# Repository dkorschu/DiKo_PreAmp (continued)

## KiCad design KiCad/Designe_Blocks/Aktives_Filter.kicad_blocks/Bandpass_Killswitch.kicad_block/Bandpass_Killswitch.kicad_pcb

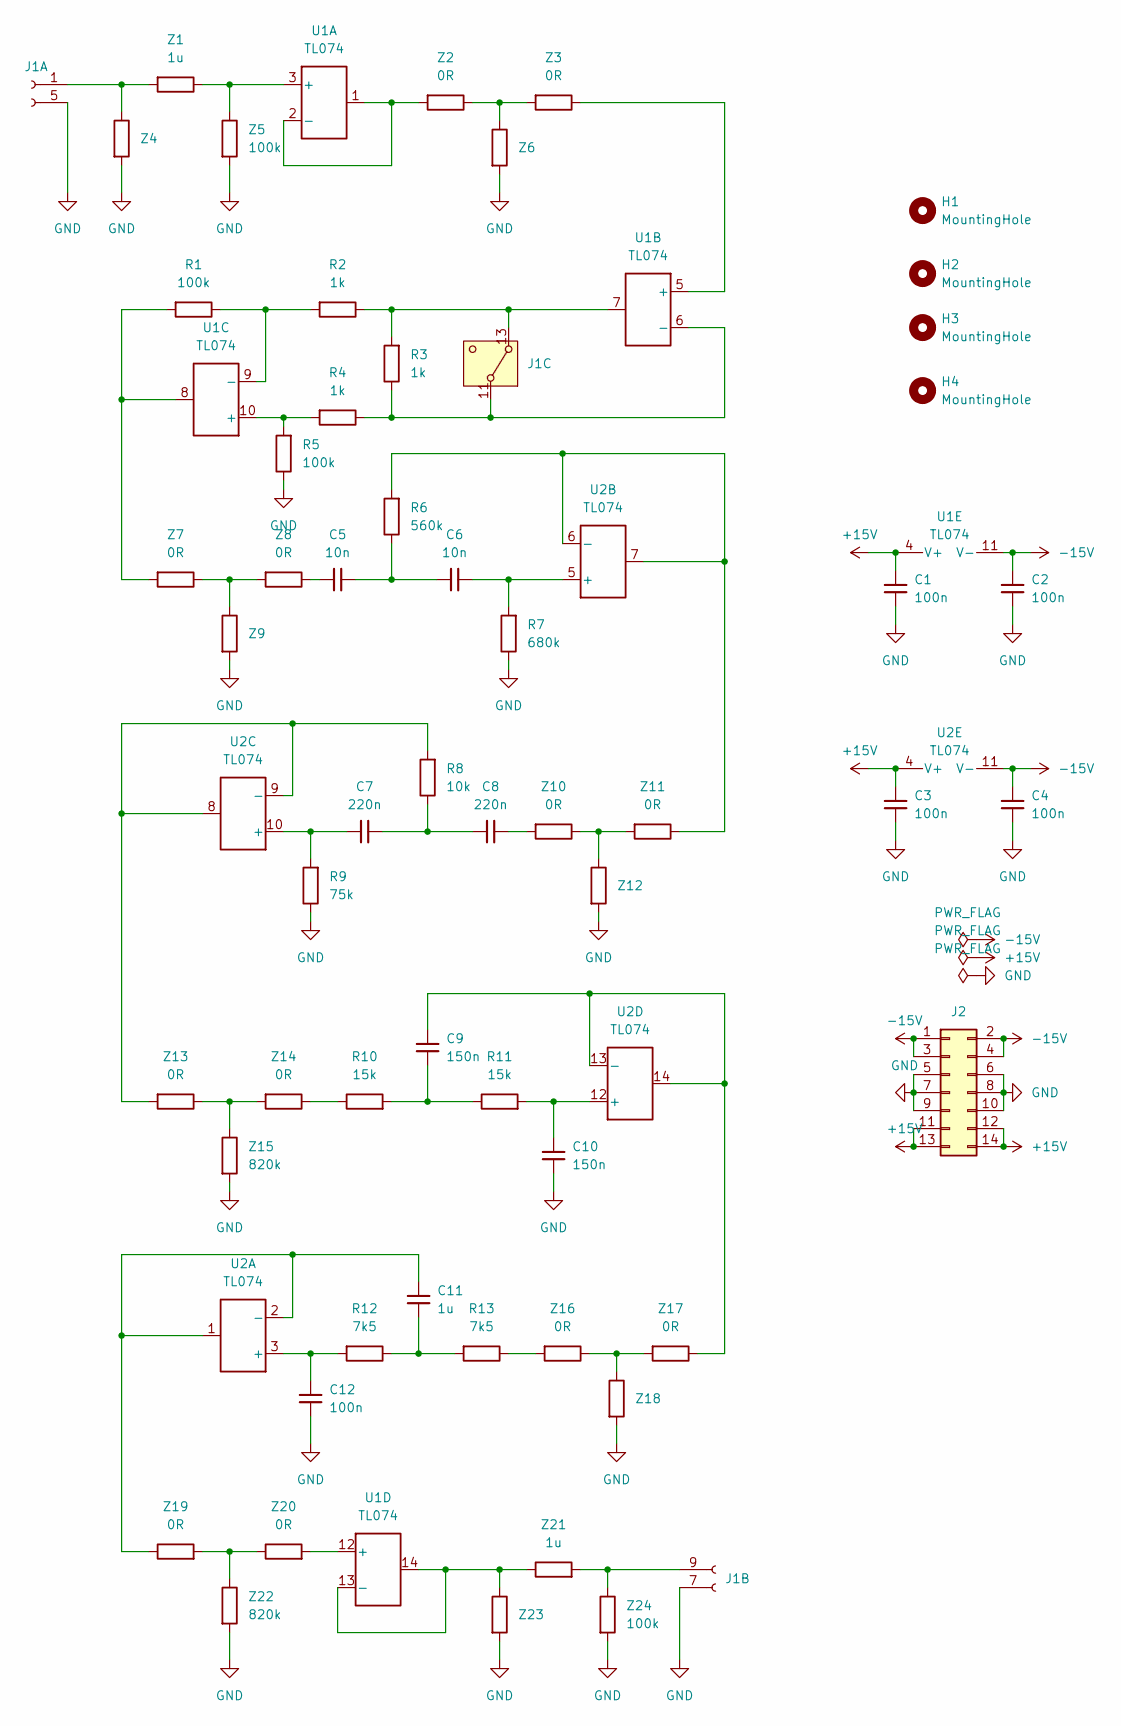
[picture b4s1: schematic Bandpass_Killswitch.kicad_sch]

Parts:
C1, C2, C3, C4, C12: 100n
C5, C6: 10n
C7, C8: 220n
C9, C10: 150n
C11: 1u
H1, H2, H3, H4: MountingHole
J1: Stecker_In_Out_Switch
J2: Conn_02x07_Odd_Even
R1, R5: 100k
R2, R3, R4: 1k
R6: 560k
R7: 680k
R8: 10k
R9: 75k
R10, R11: 15k
R12, R13: 7k5
U1, U2: TL074
Z1, Z21: 1u
Z2, Z3, Z7, Z8, Z10, Z11, Z13, Z14, Z16, Z17, Z19, Z20: 0R
Z4, Z6, Z9, Z12, Z18, Z23: (no value)
Z5, Z24: 100k
Z15, Z22: 820k

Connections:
+15V: C1.2, C3.2, J2.11, J2.12, J2.13, J2.14, U1.4 (V+), U2.4 (V+)
-15V: C2.2, C4.2, J2.1, J2.2, J2.3, J2.4, U1.11 (V-), U2.11 (V-)
unnamed: C5.1, Z8.1
unnamed: C5.2, C6.1, R6.1
unnamed: C7.1, C8.2, R8.1
unnamed: C8.1, Z10.2
unnamed: C9.1, R10.2, R11.1
unnamed: C11.1, R12.1, R13.2
unnamed: J1.9, J1.10, Z21.2, Z24.1
unnamed: J1.11 (SW_In), J1.12, R3.1, R4.1, U1.6 (-)
unnamed: J1.13 (SW_Out), J1.14, R2.1, R3.2, U1.7
unnamed: R1.2, U1.8, Z7.2
unnamed: R10.1, Z14.1
unnamed: R13.1, Z16.2
unnamed: U1.3 (+), Z1.1, Z5.1
unnamed: U1.1, U1.2 (-), Z2.2
unnamed: U1.5 (+), Z3.1
unnamed: R4.2, R5.2, U1.10 (+)
unnamed: R1.1, R2.2, U1.9 (-)
unnamed: U1.12 (+), Z20.2
unnamed: U1.13 (-), U1.14, Z21.1, Z23.1
unnamed: C12.2, R12.2, U2.3 (+)
unnamed: C11.2, U2.1, U2.2 (-), Z19.1
unnamed: C6.2, R7.2, U2.5 (+)
unnamed: R6.2, U2.6 (-), U2.7, Z11.1
unnamed: C7.2, R9.2, U2.10 (+)
unnamed: R8.2, U2.8, U2.9 (-), Z13.2
unnamed: C10.2, R11.2, U2.12 (+)
unnamed: C9.2, U2.13 (-), U2.14, Z17.1
unnamed: Z2.1, Z3.2, Z6.1
unnamed: Z7.1, Z8.2, Z9.1
unnamed: Z10.1, Z11.2, Z12.1
unnamed: Z13.1, Z14.2, Z15.1
unnamed: Z16.1, Z17.2, Z18.1
unnamed: Z19.2, Z20.1, Z22.1

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
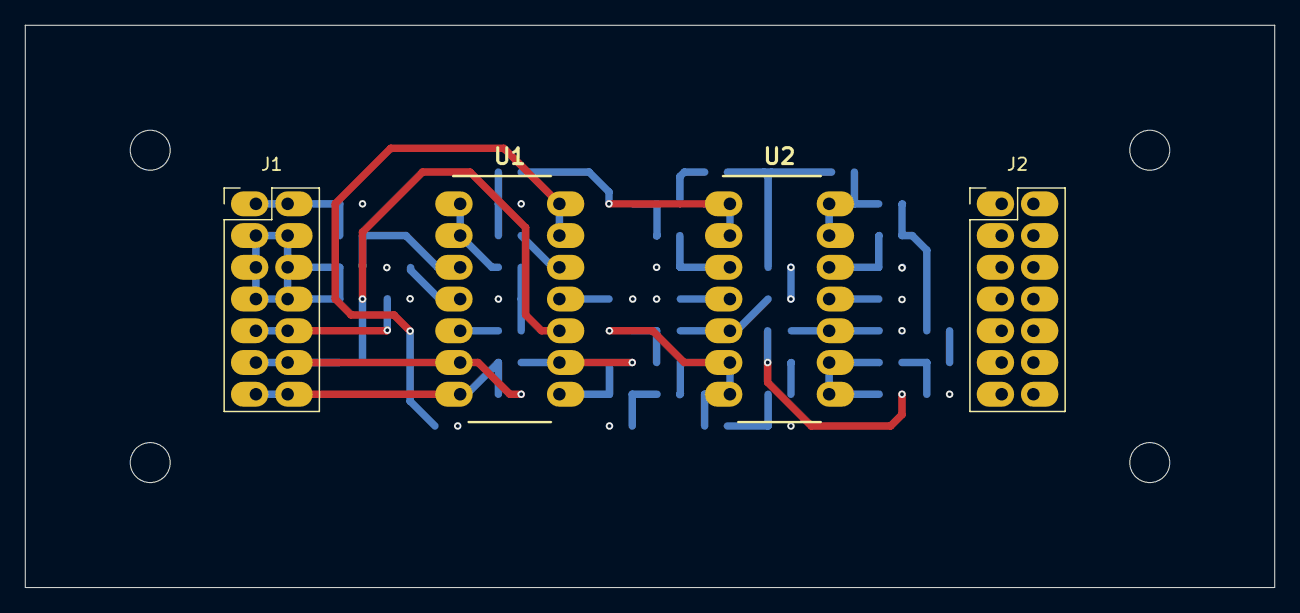
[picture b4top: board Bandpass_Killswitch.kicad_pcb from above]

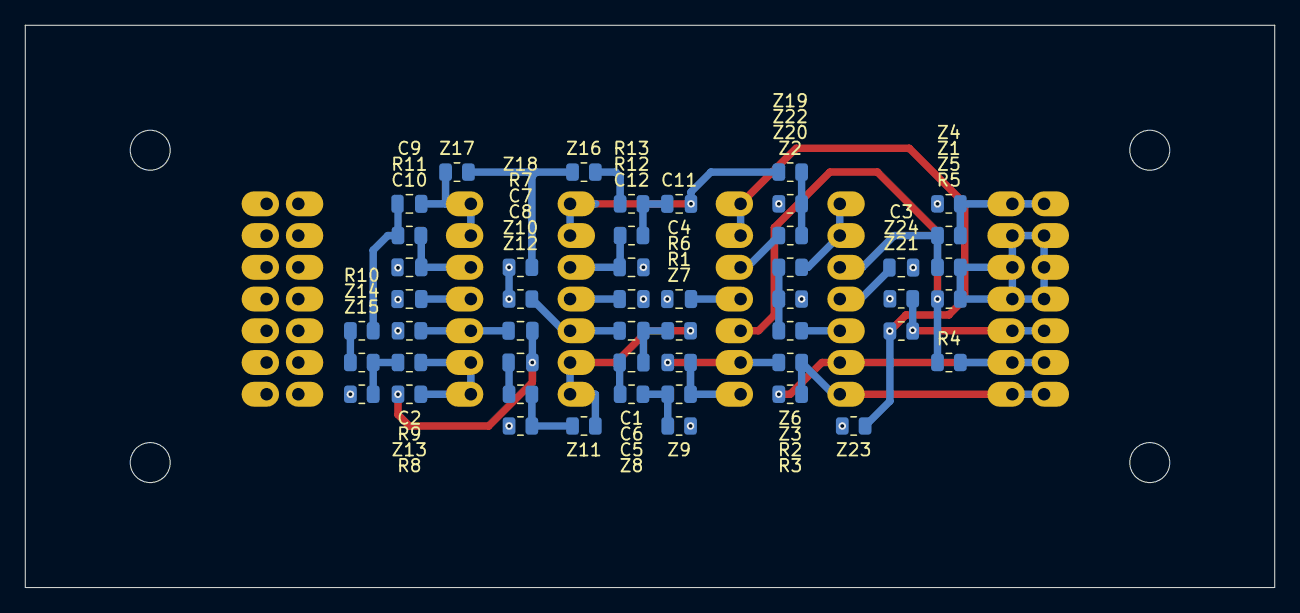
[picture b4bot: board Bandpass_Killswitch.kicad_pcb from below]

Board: 4 copper layers, 100.0 x 45.0 mm, 57 parts (49 on the bottom side), 37 nets.

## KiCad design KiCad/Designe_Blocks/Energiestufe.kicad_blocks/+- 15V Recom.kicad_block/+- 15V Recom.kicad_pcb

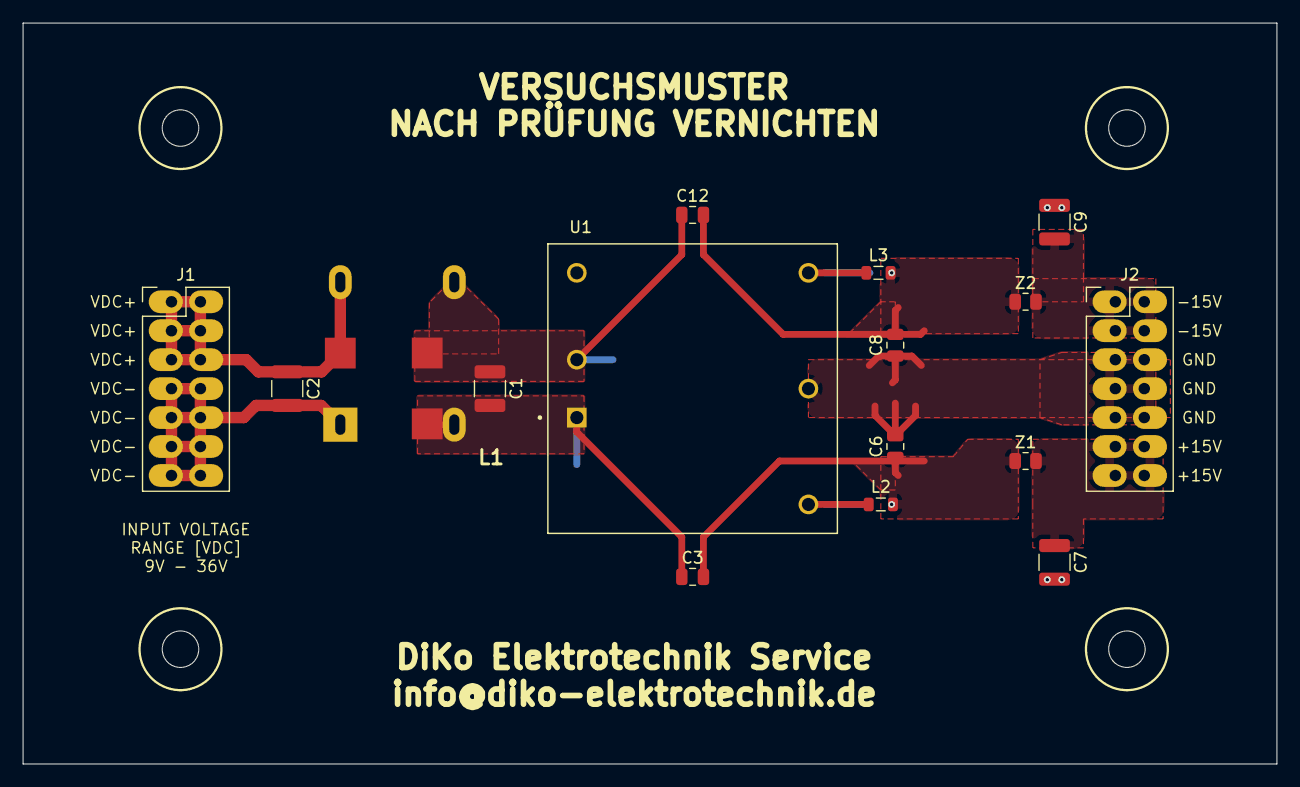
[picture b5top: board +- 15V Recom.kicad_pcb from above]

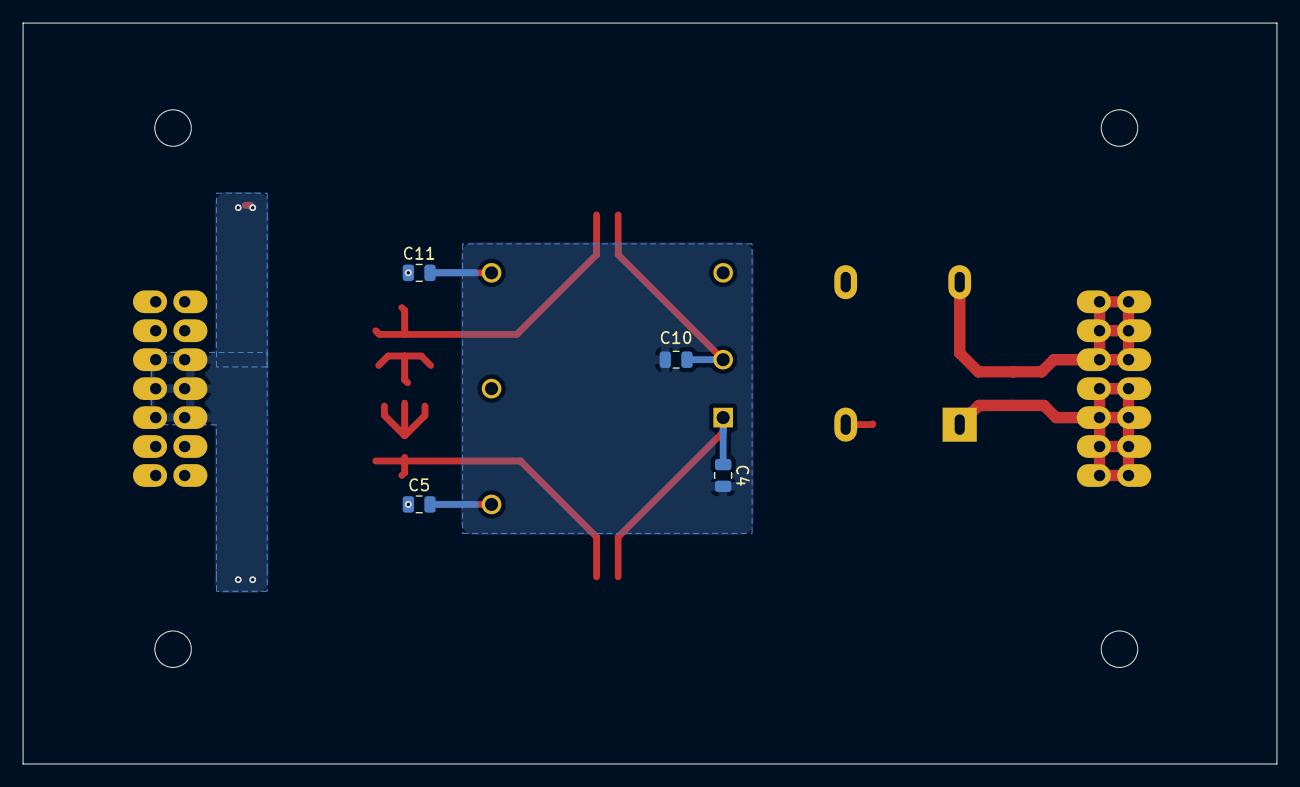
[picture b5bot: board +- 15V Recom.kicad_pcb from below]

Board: 4 copper layers, 110.0 x 65.0 mm, 24 parts (4 on the bottom side), 12 nets.

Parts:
C1, C2, C7, C9: 10u; C_1210_3225Metric
C3, C12: 470p; C_0805_2012Metric
C4, C10: 10n; C_0805_2012Metric
C5, C11: 1n; C_0805_2012Metric
C6, C8: 100n; C_0805_2012Metric
H1, H2, H3, H4: MountingHole; MountingHole_3.2mm_M3
J1: Stecker_2x7_VDC; PinHeader_2x07_P2.54mm_Vertical
J2: VCC; PinHeader_2x07_P2.54mm_Vertical
L1: WE-SL575
L2, L3: Dämpfungsperle, 220 Ohm @ 100MHz, 0.5A; L_0805_2012Metric
U1: REC10K-2415; CONV_REC10K-2415DAW_H2
Z1, Z2: 0R; R_0805_2012Metric

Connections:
+15V: C7.1, J2.11 (+15V), J2.12 (+15V), J2.13 (+15V), J2.14 (+15V), Z1.2
-15V: C9.2, J2.1 (-15V), J2.2 (-15V), J2.3 (-15V), J2.4 (-15V), Z2.2
GND: C6.2, C7.2, C8.1, C9.1, J2.5 (GND), J2.6 (GND), J2.7 (GND), J2.8 (GND), J2.9 (GND), J2.10 (GND), U1.5 (COM)
GND_FILT: C4.2, C5.2, C10.2, C11.2
unnamed: C2.1, J1.1 (VCC_In), J1.2 (VCC_In), J1.3 (VCC_In), J1.4 (VCC_In), J1.5 (VCC_In), J1.6 (VCC_In), L1.4
unnamed: C2.2, J1.7 (VCC_GND), J1.8 (VCC_GND), J1.9 (VCC_GND), J1.10 (VCC_GND), J1.11 (VCC_GND), J1.12 (VCC_GND), J1.13 (VCC_GND), J1.14 (VCC_GND), L1.1
unnamed: C3.2, C5.1, C6.1, L2.2, Z1.1
unnamed: C8.2, C11.1, C12.2, L3.2, Z2.1
unnamed: C1.2, C3.1, C4.1, L1.2, U1.1 (+VIN)
unnamed: L2.1, U1.6 (+VOUT)
unnamed: C1.1, C10.1, C12.1, L1.3, U1.2 (-VIN)
unnamed: L3.1, U1.4 (-VOUT)

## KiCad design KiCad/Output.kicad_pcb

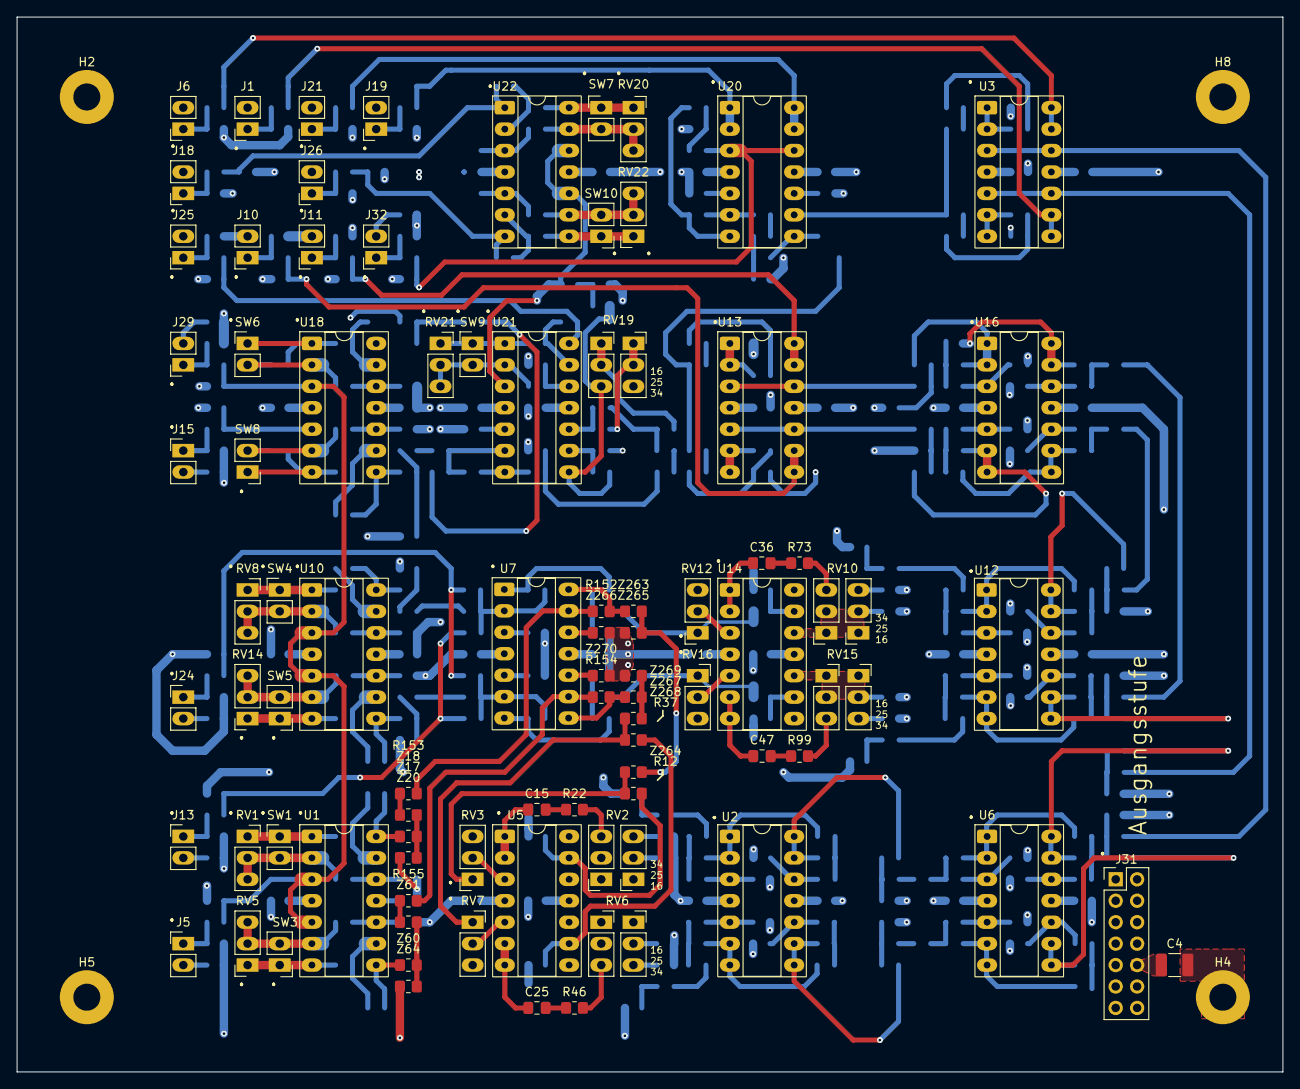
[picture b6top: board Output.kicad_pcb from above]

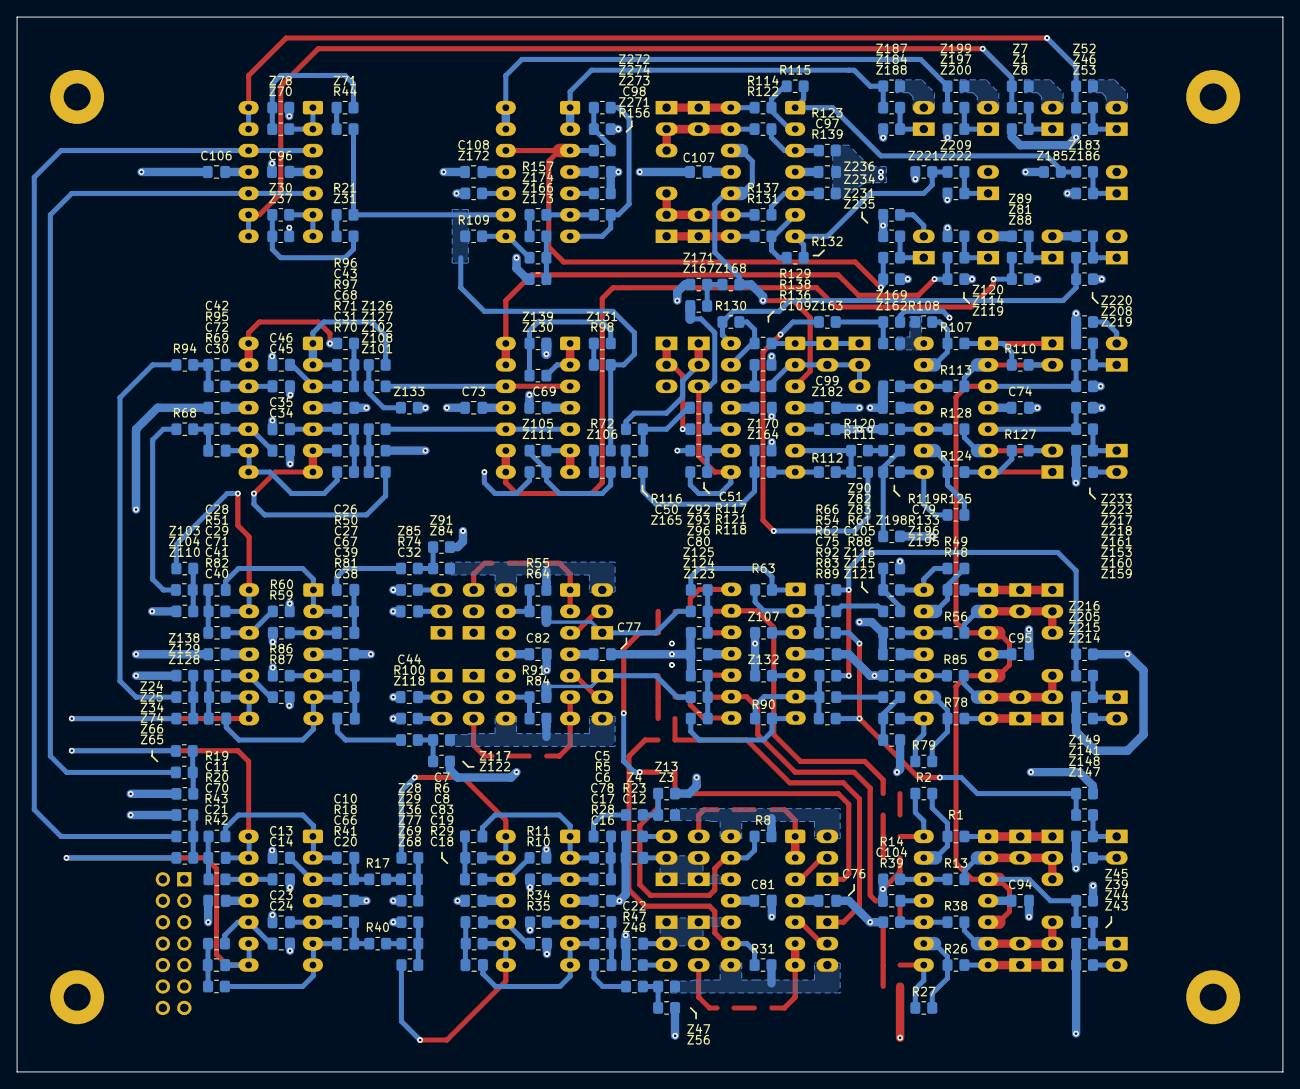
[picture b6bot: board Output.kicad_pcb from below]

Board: 4 copper layers, 150.0 x 125.0 mm, 393 parts (304 on the bottom side), 253 nets.

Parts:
C4: 10n; C_1210_3225Metric_Pad1.33x2.70mm_HandSolder
C5, C6, C7, C8, C10, C11, C13, C14, C16, C17, C18, C19, C20, C21, C23, C24, C26, C27, C28, C29, C30, C31, C34, C35, C38, C39, C40, C41, C42, C43, C45, C46: 130n; C_0805_2012Metric_Pad1.18x1.45mm_HandSolder
C12, C22, C32, C44: 470p; C_0805_2012Metric_Pad1.18x1.45mm_HandSolder
C15, C25, C36, C47: 3n; C_0805_2012Metric_Pad1.18x1.45mm_HandSolder
C50, C51: 6n8; C_0805_2012Metric_Pad1.18x1.45mm_HandSolder
C66, C67, C68, C69, C70, C71, C72, C73, C74, C75, C76, C77, C78, C79, C80, C81, C82, C83, C94, C95, C96, C97, C98, C99, C104, C105, C106, C107, C108, C109: 100n; C_0805_2012Metric_Pad1.18x1.45mm_HandSolder
H2, H5, H8: MountingHole; MountingHole_3.2mm_M3_Pad
H4: MountingHole_Pad; MountingHole_3.2mm_M3_Pad
J1: Bass_Out; PinSocket_1x02_P2.54mm_Vertical_LongPads
J5: Phono/Line_In; PinHeader_1x02_P2.54mm_Vertical_LongPads
J6: Kick_Out; PinSocket_1x02_P2.54mm_Vertical_LongPads
J10: Mid_Out; PinSocket_1x02_P2.54mm_Vertical_LongPads
J11: High_Out; PinSocket_1x02_P2.54mm_Vertical_LongPads
J13, J15, J24: Mic_Effekt_In; PinHeader_1x02_P2.54mm_Vertical_LongPads
J18: AUX_Send_1; PinSocket_1x02_P2.54mm_Vertical_LongPads
J19: Line_Out_L; PinSocket_1x02_P2.54mm_Vertical_LongPads
J21: Line_Out_R; PinSocket_1x02_P2.54mm_Vertical_LongPads
J25: AUX_Send_3; PinSocket_1x02_P2.54mm_Vertical_LongPads
J26: AUX_Send_2; PinSocket_1x02_P2.54mm_Vertical_LongPads
J29, J32: Pegel_Out; PinSocket_1x02_P2.54mm_Vertical_LongPads
J31: Conn_02x07_Odd_Even; PinHeader_2x07_P2.54mm_Vertical
R1, R26, R48, R78, R114, R129, R131: 4k7; R_0805_2012Metric_Pad1.20x1.40mm_HandSolder
R2, R21, R27, R44, R49, R54, R62, R63, R66, R72, R79, R83, R89, R90, R92, R98, R107, R108, R109, R111, R112, R115, R116, R117, R118, R120, R121, R124, R125, R130, R132, R152, R153, R154, R155, R156, R157: 10k; R_0805_2012Metric_Pad1.20x1.40mm_HandSolder
R5, R6, R10, R11, R22, R23, R28, R29, R34, R35, R46, R47, R50, R51, R59, R60, R73, R74, R81, R82, R86, R87, R99, R100: 6k8; R_0805_2012Metric_Pad1.20x1.40mm_HandSolder
R8, R12, R17, R18, R19, R20, R31, R37, R40, R41, R42, R43, R55, R64, R68, R69, R70, R71, R84, R91, R94, R95, R96, R97: 22k; R_0805_2012Metric_Pad1.20x1.40mm_HandSolder
R13, R38, R56, R85, R122, R136, R137: 470R; R_0805_2012Metric_Pad1.20x1.40mm_HandSolder
R14, R39, R61, R88, R123, R138, R139: 1k; R_0805_2012Metric_Pad1.20x1.40mm_HandSolder
R110, R113, R119, R127, R128, R133: 5k; R_0805_2012Metric_Pad1.20x1.40mm_HandSolder
RV1, RV5, RV8, RV14, RV20, RV21, RV22: 50k log; PinSocket_1x03_P2.54mm_Vertical_LongPads
RV2, RV10: 220k log; PinSocket_2x03_P2.54mm_Vertical_LongPads_Mirrored
RV3, RV7, RV12, RV16: 47k lin; PinSocket_1x03_P2.54mm_Vertical_LongPads
RV6, RV15, RV19: 220k log; PinSocket_2x03_P2.54mm_Vertical_LongPads
SW1, SW3, SW4, SW5, SW6, SW7, SW8, SW9, SW10: SW_SPDT; PinHeader_1x02_P2.54mm_Vertical_LongPads
U1, U2, U3, U5, U6, U7, U10, U12, U13, U14, U16, U18, U20, U21, U22: TL074; DIP-14_W7.62mm_Socket_LongPads
Z1, Z3, Z4, Z7, Z8, Z13, Z17, Z18, Z20, Z24, Z25, Z28, Z29, Z30, Z31, Z34, Z36, Z37, Z39, Z43, Z44, Z45, Z46, Z47, Z48, Z52, Z53, Z56, Z60, Z61, Z64, Z65, Z66, Z68, Z69, Z70, Z71, Z74, Z77, Z78, Z81, Z82, Z83, Z84, Z85, Z88, Z89, Z90, Z91, Z92, Z93, Z96, Z101, Z102, Z103, Z104, Z105, Z106, Z107, Z108, Z110, Z111, Z114, Z115, Z116, Z117, Z118, Z119, Z120, Z121, Z122, Z123, Z124, Z125, Z126, Z127, Z128, Z129, Z130, Z131, Z132, Z133, Z138, Z139, Z141, Z147, Z148, Z149, Z153, Z159, Z160, Z161, Z162, Z163, Z164, Z165, Z166, Z167, Z168, Z169, Z170, Z171, Z172, Z173, Z174, Z182, Z183, Z184, Z185, Z186, Z187, Z188, Z195, Z196, Z197, Z198, Z199, Z200, Z205, Z208, Z209, Z214, Z215, Z216, Z217, Z218, Z219, Z220, Z221, Z222, Z223, Z231, Z233, Z234, Z235, Z236, Z263, Z264, Z265, Z266, Z267, Z268, Z269, Z270, Z271, Z272, Z273, Z274: R_0805_2012Metric_Pad1.20x1.40mm_HandSolder

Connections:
9V_GND_O: J31.1, J31.2, J31.3, J31.4
+9V_O: J31.5, J31.6
+15V_O: C66.2, C67.2, C68.2, C69.2, C74.2, C75.2, C76.2, C77.2, C78.2, C94.2, C95.2, C96.2, C97.2, C98.2, C99.2, J31.13, J31.14, U1.4 (V+), U2.4 (V+), U3.4 (V+), U5.4 (V+), U6.4 (V+), U7.4 (V+), U10.4 (V+), U12.4 (V+), U13.4 (V+), U14.4 (V+), U16.4 (V+), U18.4 (V+), U20.4 (V+), U21.4 (V+), U22.4 (V+)
-15V_O: C70.2, C71.2, C72.2, C73.2, C79.2, C80.2, C81.2, C82.2, C83.2, C104.2, C105.2, C106.2, C107.2, C108.2, C109.2, J31.7, J31.8, U1.11 (V-), U2.11 (V-), U3.11 (V-), U5.11 (V-), U6.11 (V-), U7.11 (V-), U10.11 (V-), U12.11 (V-), U13.11 (V-), U14.11 (V-), U16.11 (V-), U18.11 (V-), U20.11 (V-), U21.11 (V-), U22.11 (V-)
GND_O: C4.2, C12.2, C13.1, C14.1, C22.2, C23.1, C24.1, C32.2, C34.1, C35.1, C44.2, C45.1, C46.1, C66.1, C67.1, C68.1, C69.1, C70.1, C71.1, C72.1, C73.1, C74.1, C75.1, C76.1, C77.1, C78.1, C79.1, C80.1, C81.1, C82.1, C83.1, C94.1, C95.1, C96.1, C97.1, C98.1, C99.1, C104.1, C105.1, C106.1, C107.1, C108.1, C109.1, J1.2, J6.2, J10.2, J11.2, J18.2, J19.2, J21.2, J25.2, J26.2, J31.9, J31.10, J31.11, J31.12, R10.1, R11.1, R14.1, R23.1, R34.1, R35.1, R39.1, R47.1, R59.1, R60.1, R61.1, R74.1, R86.1, R87.1, R88.1, R100.1, R119.2, R121.2, R123.2, R133.2, R138.2, R139.2, RV19.4, Z7.2, Z8.2, Z13.2, Z20.2, Z34.2, Z36.2, Z37.2, Z43.2, Z44.2, Z45.2, Z52.2, Z53.2, Z56.2, Z64.2, Z74.2, Z77.2, Z78.2, Z88.2, Z89.2, Z90.2, Z91.2, Z96.2, Z107.2, Z108.2, Z110.2, Z111.2, Z119.2, Z120.2, Z121.2, Z122.2, Z125.2, Z132.2, Z133.2, Z138.2, Z139.2, Z147.2, Z148.2, Z149.2, Z159.2, Z160.2, Z161.2, Z169.2, Z170.2, Z171.2, Z172.2, Z173.2, Z182.2, Z185.2, Z186.2, Z187.2, Z188.2, Z198.2, Z199.2, Z200.2, Z214.2, Z215.2, Z216.2, Z218.2, Z219.2, Z220.2, Z221.2, Z222.2, Z223.2, Z233.2, Z234.2, Z235.2, Z236.2, Z265.2, Z266.2, Z269.2, Z270.2, Z271.2, Z274.2
unnamed: C4.1, H4.1
unnamed: C5.1, Z4.2
unnamed: C5.2, C6.1, R5.1
unnamed: C7.2, C8.1, R6.1
unnamed: C10.1, R17.2, R18.1
unnamed: C11.1, R19.2, R20.1
unnamed: C15.1, R22.1
unnamed: C16.1, Z48.2
unnamed: C16.2, C17.1, R28.1
unnamed: C18.2, C19.1, R29.1
unnamed: C20.1, R40.2, R41.1
unnamed: C21.1, R42.2, R43.1
unnamed: C25.1, R46.1
unnamed: C26.1, Z85.2
unnamed: C26.2, C27.1, R50.1
unnamed: C28.2, C29.1, R51.1
unnamed: C30.1, R68.2, R69.1
unnamed: C31.1, R70.2, R71.1
unnamed: C36.1, R73.1
unnamed: C38.1, Z118.2
unnamed: C38.2, C39.1, R81.1
unnamed: C40.2, C41.1, R82.1
unnamed: C42.1, R94.2, R95.1
unnamed: C43.1, R96.2, R97.1
unnamed: C47.1, R99.1
unnamed: C50.1, C51.2, R116.1
unnamed: C50.2, Z165.2
unnamed: J1.1, Z1.2, Z8.1
unnamed: J5.1, Z39.1, Z44.1
unnamed: J5.2, Z43.1
unnamed: J6.1, Z46.2, Z53.1
unnamed: J10.1, Z81.2, Z89.1
unnamed: J11.1, Z114.2, Z120.1
unnamed: J13.1, Z141.1, Z148.1
unnamed: J13.2, Z147.1
unnamed: J15.1, Z153.1, Z160.1
unnamed: J15.2, Z159.1
unnamed: J18.1, Z183.2, Z186.1
unnamed: J19.1, Z184.2, Z188.1
unnamed: J21.1, Z197.2, Z200.1
unnamed: J24.1, Z205.1, Z215.1
unnamed: J24.2, Z214.1
unnamed: J25.1, Z208.2, Z220.1
unnamed: J26.1, Z209.2, Z222.1
unnamed: J29.1, Z217.2, Z223.1
unnamed: J29.2, Z233.1
unnamed: J32.1, Z231.1, Z234.1
unnamed: J32.2, Z236.1
unnamed: R2.2, U1.14, Z17.1
unnamed: R8.2, RV3.3, U5.14, Z3.1
unnamed: R12.1, RV3.1, Z264.2
unnamed: R17.1, Z29.2
unnamed: R21.1, Z31.2
unnamed: R22.2, RV2.3
unnamed: R23.2, RV2.4
unnamed: R27.2, U1.8, Z60.1
unnamed: R31.2, RV7.3, U5.8, Z47.1
unnamed: R37.1, RV7.1, Z268.2
unnamed: R40.1, Z69.2
unnamed: R44.1, Z71.2
unnamed: R46.2, RV6.3
unnamed: R47.2, RV6.4
unnamed: R49.2, U10.14, Z82.1
unnamed: R54.1, Z83.2
unnamed: R55.2, RV12.3, U14.14, Z84.1
unnamed: R62.1, R89.1, Z141.2, Z149.1
unnamed: R63.2, U7.1, Z92.1
unnamed: R64.1, RV12.1, Z93.2
unnamed: R66.1, R92.1, Z205.2, Z216.1
unnamed: R68.1, Z104.2
unnamed: R72.1, Z106.2
unnamed: R73.2, RV10.3
unnamed: R74.2, RV10.4
unnamed: R79.2, U10.8, Z115.1
unnamed: R83.1, Z116.2
unnamed: R84.2, RV16.3, U14.8, Z117.1
unnamed: R90.2, U7.7, Z123.1
unnamed: R91.1, RV16.1, Z124.2
unnamed: R94.1, Z129.2
unnamed: R98.1, Z131.2
unnamed: R99.2, RV15.3
unnamed: R100.2, RV15.4
unnamed: R108.1, U18.14, Z162.1
unnamed: R109.2, U20.8, Z166.1
unnamed: R111.2, Z163.2
unnamed: R112.1, U21.7, Z164.1
unnamed: R115.1, U22.1, Z183.1, Z185.1
unnamed: R116.2, RV19.1, RV19.2
unnamed: R117.2, RV19.5, RV19.6
unnamed: R118.1, RV19.3, U21.8, Z167.1
unnamed: R120.2, Z196.2
unnamed: R125.1, U18.8, Z195.1
unnamed: R130.1, U21.14, Z208.1, Z219.1
unnamed: R132.1, U22.7, Z209.1, Z221.1
unnamed: R152.2, U7.14, Z263.1
unnamed: R153.1, Z18.2
unnamed: R154.2, U7.8, Z267.1
unnamed: R155.1, Z61.2
unnamed: R156.1, U20.7, Z272.1
unnamed: R157.1, Z174.2
unnamed: R1.1, RV1.1, SW1.1 (A), U1.1
unnamed: R13.1, RV1.2, RV1.3, SW1.2 (B), U1.2 (-)
unnamed: R26.1, RV5.1, SW3.1 (A), U1.7
unnamed: R38.1, RV5.2, RV5.3, SW3.2 (B), U1.6 (-)
unnamed: R48.1, RV8.1, SW4.1 (A), U10.1
unnamed: R56.1, RV8.2, RV8.3, SW4.2 (B), U10.2 (-)
unnamed: R78.1, RV14.1, SW5.1 (A), U10.7
unnamed: R85.1, RV14.2, RV14.3, SW5.2 (B), U10.6 (-)
unnamed: R107.2, R110.1, SW6.1 (A), U18.1
unnamed: R110.2, R113.2, SW6.2 (B), U18.2 (-)
unnamed: R114.2, RV20.1, SW7.1 (A), U22.14
unnamed: R122.2, RV20.2, RV20.3, SW7.2 (B), U22.13 (-)
unnamed: R124.2, R127.1, SW8.1 (A), U18.7
unnamed: R127.2, R128.2, SW8.2 (B), U18.6 (-)
unnamed: R129.2, RV21.1, SW9.1 (A), U21.1
unnamed: R136.2, RV21.2, RV21.3, SW9.2 (B), U21.2 (-)
unnamed: R131.2, RV22.1, SW10.1 (A), U22.8
unnamed: R137.2, RV22.2, RV22.3, SW10.2 (B), U22.9 (-)
unnamed: R38.2, R39.2, U1.10 (+)
unnamed: R26.2, R27.1, U1.9 (-)
unnamed: R13.2, R14.2, U1.12 (+)
unnamed: R1.2, R2.1, U1.13 (-)
unnamed: C6.2, R10.2, U2.3 (+)
unnamed: C7.1, R5.2, U2.1, U2.2 (-)
unnamed: C17.2, R34.2, U2.5 (+)
unnamed: C18.1, R28.2, U2.6 (-), U2.7
unnamed: C19.2, R35.2, U2.10 (+)
unnamed: R29.2, U2.8, U2.9 (-), Z68.1
unnamed: C8.2, R11.2, U2.12 (+)
unnamed: R6.2, U2.13 (-), U2.14, Z28.1
unnamed: U3.3 (+), U3.12 (+), Z66.2
unnamed: U3.1, U3.2 (-), Z70.1
unnamed: U3.5 (+), U3.10 (+), Z25.2
unnamed: U3.6 (-), U3.7, Z30.1
unnamed: U3.8, U3.9 (-), Z1.1, Z7.1
unnamed: U3.13 (-), U3.14, Z46.1, Z52.1
unnamed: RV3.2, U5.3 (+)
unnamed: C15.2, U5.1, U5.2 (-)
unnamed: RV7.2, U5.5 (+)
unnamed: C25.2, U5.6 (-), U5.7
unnamed: C22.1, RV6.1, RV6.2, RV6.5, RV6.6, U5.10 (+)
unnamed: R31.1, R37.2, U5.9 (-)
unnamed: C12.1, RV2.1, RV2.2, RV2.5, RV2.6, U5.12 (+)
unnamed: R8.1, R12.2, U5.13 (-)
unnamed: C13.2, R18.2, U6.3 (+)
unnamed: C10.2, R19.1, U6.1, U6.2 (-)
unnamed: C23.2, R41.2, U6.5 (+)
unnamed: C20.2, R42.1, U6.6 (-), U6.7
unnamed: C24.2, R43.2, U6.10 (+)
unnamed: C21.2, U6.8, U6.9 (-), Z65.1
unnamed: C14.2, R20.2, U6.12 (+)
unnamed: C11.2, U6.13 (-), U6.14, Z24.1
unnamed: U7.3 (+), Z107.1
unnamed: R54.2, R62.2, R63.1, R66.2, U7.2 (-)
unnamed: U7.5 (+), Z132.1
unnamed: R83.2, R89.2, R90.1, R92.2, U7.6 (-)
unnamed: U7.10 (+), Z270.1
unnamed: R154.1, R155.2, U7.9 (-)
unnamed: U7.12 (+), Z266.1
unnamed: R152.1, R153.2, U7.13 (-)
unnamed: U1.3 (+), U1.5 (+), U10.3 (+), U10.5 (+), U18.3 (+), Z39.2, Z45.1, Z217.1, Z218.1
unnamed: R85.2, R88.2, U10.10 (+)
unnamed: R78.2, R79.1, U10.9 (-)
unnamed: R56.2, R61.2, U10.12 (+)
unnamed: R48.2, R49.1, U10.13 (-)
unnamed: C27.2, R59.2, U12.3 (+)
unnamed: C28.1, R50.2, U12.1, U12.2 (-)
unnamed: C39.2, R86.2, U12.5 (+)
unnamed: C40.1, R81.2, U12.6 (-), U12.7
unnamed: C41.2, R87.2, U12.10 (+)
unnamed: R82.2, U12.8, U12.9 (-), Z128.1
unnamed: C29.2, R60.2, U12.12 (+)
unnamed: R51.2, U12.13 (-), U12.14, Z103.1
unnamed: U13.3 (+), U13.12 (+), Z127.2
unnamed: U13.1, U13.2 (-), Z130.1
unnamed: U13.5 (+), U13.10 (+), Z102.2
unnamed: U13.6 (-), U13.7, Z105.1
unnamed: U13.8, U13.9 (-), Z81.1, Z88.1
unnamed: U13.13 (-), U13.14, Z114.1, Z119.1
unnamed: RV12.2, U14.3 (+)
unnamed: C36.2, U14.1, U14.2 (-)
unnamed: RV16.2, U14.5 (+)
unnamed: C47.2, U14.6 (-), U14.7
unnamed: C44.1, RV15.1, RV15.2, RV15.5, RV15.6, U14.10 (+)
unnamed: R84.1, R91.2, U14.9 (-)
unnamed: C32.1, RV10.1, RV10.2, RV10.5, RV10.6, U14.12 (+)
unnamed: R55.1, R64.2, U14.13 (-)
unnamed: C46.2, R97.2, U16.3 (+)
unnamed: C43.2, U16.1, U16.2 (-), Z126.1
unnamed: C35.2, R71.2, U16.5 (+)
unnamed: C31.2, U16.6 (-), U16.7, Z101.1
unnamed: C34.2, R69.2, U16.10 (+)
unnamed: C30.2, R70.1, U16.8, U16.9 (-)
unnamed: C45.2, R95.2, U16.12 (+)
unnamed: C42.2, R96.1, U16.13 (-), U16.14
unnamed: U18.5 (+), Z153.2, Z161.1
unnamed: R128.1, R133.1, U18.10 (+)
unnamed: R124.1, R125.2, U18.9 (-)
unnamed: R113.1, R119.1, U18.12 (+)
unnamed: R107.1, R108.2, U18.13 (-)
unnamed: U20.3 (+), U20.12 (+), Z231.2, Z235.1, Z273.2
unnamed: U20.1, U20.2 (-), Z184.1, Z187.1
unnamed: U20.5 (+), Z271.1
unnamed: R156.2, R157.2, U20.6 (-)
unnamed: U20.10 (+), Z172.1
unnamed: R21.2, R44.2, R72.2, R98.2, R109.1, U20.9 (-)
unnamed: U20.13 (-), U20.14, Z197.1, Z199.1
unnamed: U21.3 (+), U22.10 (+), U22.12 (+), Z168.2
unnamed: U21.5 (+), Z182.1
unnamed: R111.1, R112.2, R120.1, U21.6 (-)
unnamed: C51.1, R117.1, U21.10 (+)
unnamed: R118.2, R121.1, U21.9 (-)
unnamed: R136.1, R138.1, U21.12 (+)
unnamed: R129.1, R130.2, U21.13 (-)
unnamed: R122.1, R123.1, U22.3 (+)
unnamed: R114.1, R115.2, U22.2 (-)
unnamed: R137.1, R139.1, U22.5 (+)
unnamed: R131.1, R132.2, U22.6 (-)
unnamed: Z3.2, Z4.1, Z13.1
unnamed: Z17.2, Z18.1, Z20.1
unnamed: Z24.2, Z25.1, Z34.1
unnamed: Z28.2, Z29.1, Z36.1
unnamed: Z30.2, Z31.1, Z37.1
unnamed: Z47.2, Z48.1, Z56.1
unnamed: Z60.2, Z61.1, Z64.1
unnamed: Z65.2, Z66.1, Z74.1
unnamed: Z68.2, Z69.1, Z77.1
unnamed: Z70.2, Z71.1, Z78.1
unnamed: Z82.2, Z83.1, Z90.1
unnamed: Z84.2, Z85.1, Z91.1
unnamed: Z92.2, Z93.1, Z96.1
unnamed: Z101.2, Z102.1, Z108.1
unnamed: Z103.2, Z104.1, Z110.1
unnamed: Z105.2, Z106.1, Z111.1
unnamed: Z115.2, Z116.1, Z121.1
unnamed: Z117.2, Z118.1, Z122.1
unnamed: Z123.2, Z124.1, Z125.1
unnamed: Z126.2, Z127.1, Z133.1
unnamed: Z128.2, Z129.1, Z138.1
unnamed: Z130.2, Z131.1, Z139.1
unnamed: Z162.2, Z163.1, Z169.1
unnamed: Z164.2, Z165.1, Z170.1
unnamed: Z166.2, Z173.1, Z174.1
unnamed: Z167.2, Z168.1, Z171.1
unnamed: Z195.2, Z196.1, Z198.1
unnamed: Z263.2, Z264.1, Z265.1
unnamed: Z267.2, Z268.1, Z269.1
unnamed: Z272.2, Z273.1, Z274.1
